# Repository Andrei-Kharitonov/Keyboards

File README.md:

# My keyboards
All my keyboards, that i made.

## Keebs:
- [first-split36](https://github.com/Andrei-Kharitonov/Keyboards/tree/main/first-split36) - my first build 36 key split column staggered (pcb only).
- [monolith34](https://github.com/Andrei-Kharitonov/Keyboards/tree/main/monolith34) - 34 key 3d printed handwired ortholinear keyboard with unusual bottom row.
- [Sofle-rgb case](https://github.com/Andrei-Kharitonov/Keyboards/tree/main/Sofle-rgb) - 3d print case for Sofle rgb

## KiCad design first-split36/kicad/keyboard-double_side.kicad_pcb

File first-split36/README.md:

# First-split36
36 key split column staggered keyboard. Use Pro Micro microcontroller and crkbd firmware. Mirror boards.

## Photos

## Parts
- 2x Arduino Pro Micro (Atmega32U4)
- 2x trrs connectors
- 1x 3,5mm audio cabel
- 36x cherry mx switches
- 36x d3 smd diods

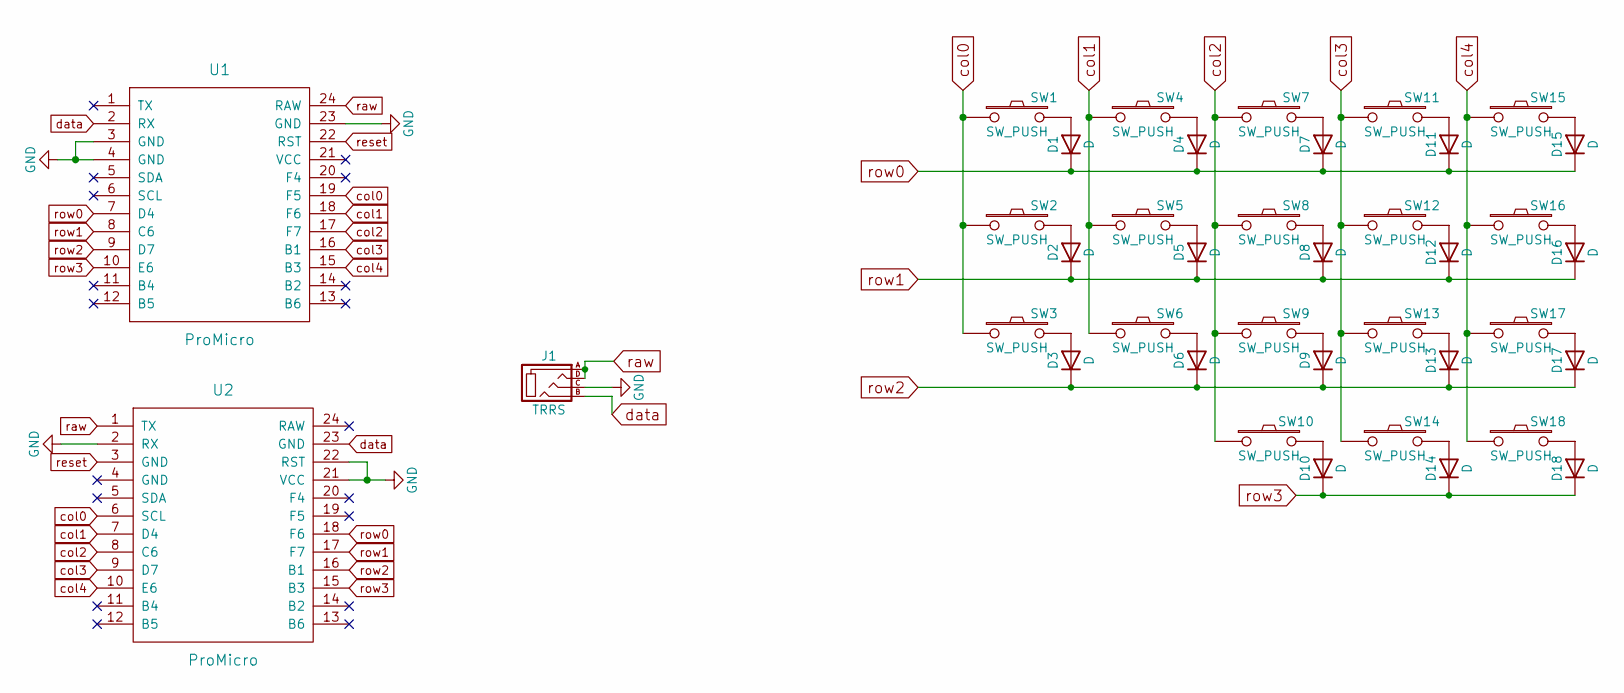
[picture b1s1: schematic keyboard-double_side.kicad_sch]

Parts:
D1, D2, D3, D4, D5, D6, D7, D8, D9, D10, D11, D12, D13, D14, D15, D16, D17, D18: D; SOD_123
J1: TRRS
SW1, SW2, SW3, SW4, SW5, SW6, SW7, SW8, SW9, SW10, SW11, SW12, SW13, SW14, SW15, SW16, SW17, SW18: SW_PUSH; SW_Cherry_ds
U1, U2: ProMicro

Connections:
GND: J1.C, U1.3 (GND), U1.4 (GND), U1.23 (GND), U2.2 (RX), U2.21 (VCC), U2.22 (RST)
unnamed: D1.2 (A), SW1.2
unnamed: D2.2 (A), SW2.2
unnamed: D3.2 (A), SW3.2
unnamed: D4.2 (A), SW4.2
unnamed: D5.2 (A), SW5.2
unnamed: D6.2 (A), SW6.2
unnamed: D7.2 (A), SW7.2
unnamed: D8.2 (A), SW8.2
unnamed: D9.2 (A), SW9.2
unnamed: D10.2 (A), SW10.2
unnamed: D11.2 (A), SW11.2
unnamed: D12.2 (A), SW12.2
unnamed: D13.2 (A), SW13.2
unnamed: D14.2 (A), SW14.2
unnamed: D15.2 (A), SW15.2
unnamed: D16.2 (A), SW16.2
unnamed: D17.2 (A), SW17.2
unnamed: D18.2 (A), SW18.2
col0: SW1.1, SW2.1, SW3.1, U1.19 (F5), U2.6 (SCL)
col1: SW4.1, SW5.1, SW6.1, U1.18 (F6), U2.7 (D4)
col2: SW7.1, SW8.1, SW9.1, SW10.1, U1.17 (F7), U2.8 (C6)
col3: SW11.1, SW12.1, SW13.1, SW14.1, U1.16 (B1), U2.9 (D7)
col4: SW15.1, SW16.1, SW17.1, SW18.1, U1.15 (B3), U2.10 (E6)
data: J1.B, U1.2 (RX), U2.23 (GND)
raw: J1.A, J1.D, U1.24 (RAW), U2.1 (TX)
reset: U1.22 (RST), U2.3 (GND)
row0: D1.1 (K), D4.1 (K), D7.1 (K), D11.1 (K), D15.1 (K), U1.7 (D4), U2.18 (F6)
row1: D2.1 (K), D5.1 (K), D8.1 (K), D12.1 (K), D16.1 (K), U1.8 (C6), U2.17 (F7)
row2: D3.1 (K), D6.1 (K), D9.1 (K), D13.1 (K), D17.1 (K), U1.9 (D7), U2.16 (B1)
row3: D10.1 (K), D14.1 (K), D18.1 (K), U1.10 (E6), U2.15 (B3)

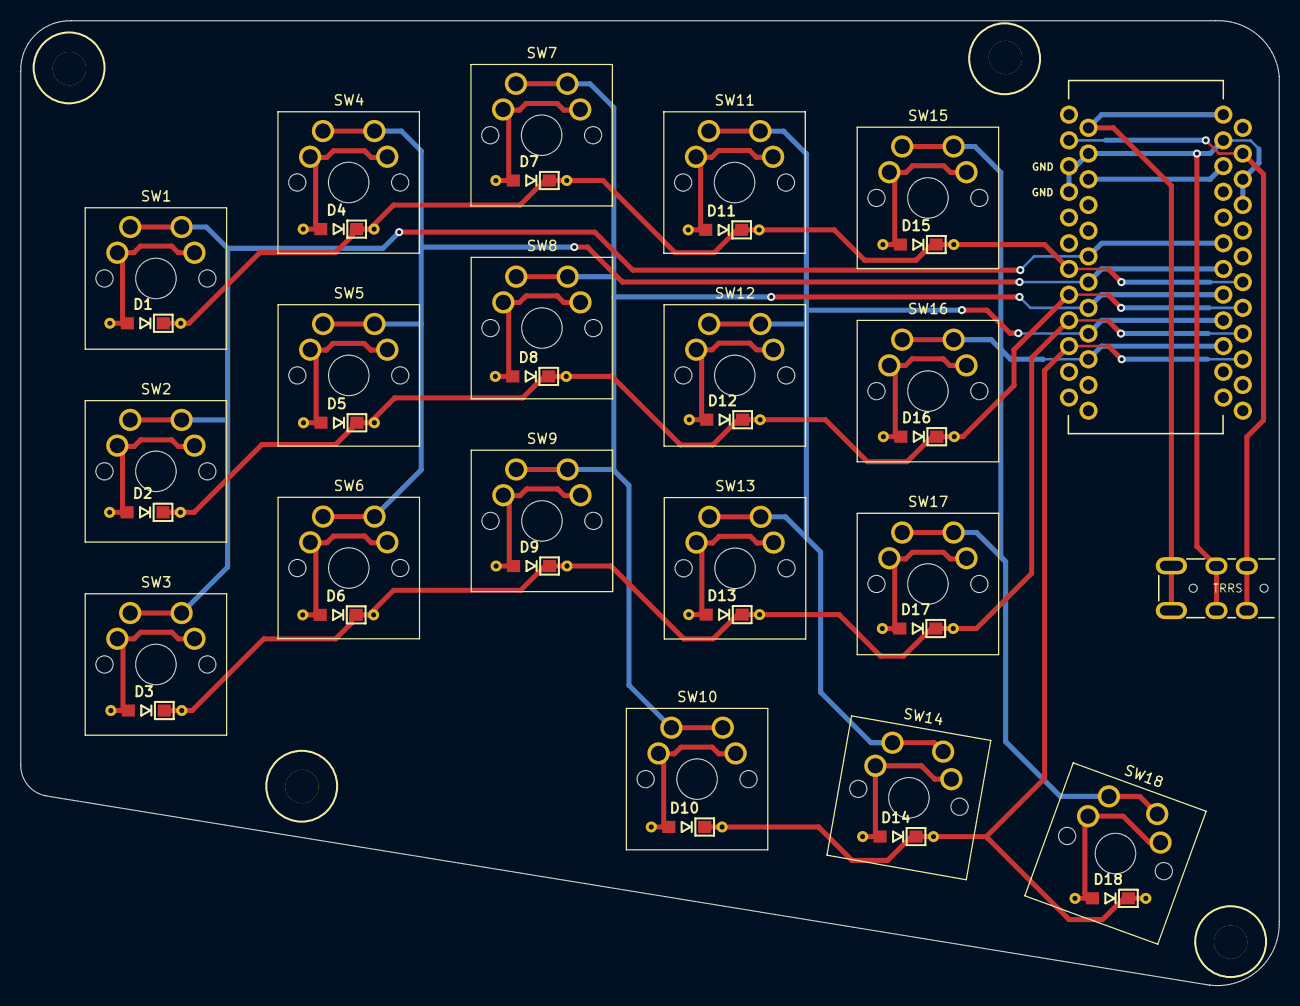
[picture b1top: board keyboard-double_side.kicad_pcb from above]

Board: 2 copper layers, 124.3 x 95.3 mm, 39 parts (0 on the bottom side), 31 nets.

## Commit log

2023-01-31 Init
2023-01-31 New keyboard: first-split36
2023-01-31 New keyboard: monolith34
2023-02-03 Changed layout
2025-11-11 added stl for sofle case, added photos
2025-12-12 firstsplit36 added vial, sofle updated layout
2025-12-12 firstsplit36 fixed volume control
